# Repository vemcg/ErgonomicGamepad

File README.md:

# ErgonomicGamepad

Custom ergonomic gaming keypad PCB project (KiCad) with a 4x6 key matrix, hot-swap sockets, and USB-C.

## Overview

This repo contains the schematic, PCB, and production support files for an ATmega32U4-based ergonomic keypad.

## Hardware Summary

| Item | Value |
|---|---|
| MCU | ATmega32U4 (TQFP-44) |
| Key Matrix | 4 rows x 6 columns (24 keys) |
| Switch Interface | MX-compatible Kailh hot-swap sockets |
| USB | USB-C receptacle |
| Clock | 16 MHz crystal |
| Passive Size | 0603 resistors/capacitors |
| Protection/Diodes | 1N4148 matrix diodes, 1N5819WS Schottky |

## Core Project Files

- `ErgonomicGamepad.kicad_sch` - Schematic
- `ErgonomicGamepad.kicad_pcb` - PCB layout
- `ErgonomicGamepad.kicad_pro` - KiCad project
- `jlcpcb/production_files/jlc_sourcing_bom_template.csv` - Main sourcing/BOM table
- `jlcpcb/production_files/verify_stock_before_ordering.csv` - Pre-order stock/sourcing risk checklist (MCU lead time, hand-sourced sockets/connectors/switches)
- `jlcpcb/gerber/` - Manufacturing output folder

## Pinout Baseline

### Matrix

| Signal | Pins |
|---|---|
| ROW1-ROW4 | PF7, PF6, PF5, PF4 |
| COL1-COL6 | PD1, PD2, PD3, PD4, PD5, PD6 |

### Programming Header (ISP)

| Signal | Pin Mapping |
|---|---|
| SCK | PB1 |
| MOSI | PB2 |
| MISO | PB3 |
| RESET | J5 pin 5 -> U1 ~RESET |

## USB-C Implementation (Resolved)

J1 is an HRO `TYPE-C-31-M-12` receptacle - hybrid retention (SMT signal/power
pins plus through-hole shell tabs) for stronger cable-insertion durability
than an SMT-only part. This is a USB 2.0 device-only implementation (power +
D+/D-); no SuperSpeed/Alt-Mode pins are used.

- **Orientation**: fully reversible. Both D+ pads (A6 and B6) are tied
  together at the connector, and both D- pads (A7 and B7) are tied together,
  so the plug works in either orientation.
- **Signal path**: connector D+/D- -> U2 (`USBLC6-2SC6` ESD protection array)
  -> series resistors R1/R2 (20R) -> U1 D-/D+ pins, with TP3/TP4 tapping the
  MCU-side D-/D+ nets for debug access.
- **CC (device-mode/UFP)**: CC1 and CC2 each pull down to GND through a 5.1k
  resistor (R4, R5) - the standard passive UFP presentation, no CC logic IC.
- **Shield/GND**: J1's shield pin (`SH`) ties directly to GND (no RC/ferrite
  isolation).
- **Power path**: VBUS feeds +5V through D1 (`1N5819WS` Schottky) gated by
  JP1 (power-path select jumper - see Jumper Shunts below); J7 (external
  2-pin power connector) feeds +5V directly. The Schottky prevents VBUS from
  being back-fed if J7 external power is connected while a USB cable is also
  plugged in.

## Debug / Test Points

- **TP1-TP7**: internal signal debug points (power-select node, GND
  reference, USB D+/D-, crystal XTAL1/XTAL2, USB regulator cap node) using
  the small `TestPoint_Pad_D1.5mm` footprint - sized for a fine meter probe
  or hook, not a full-size clip.
- **TP8 (+5V) / TP9 (GND)**: dedicated power-rail clip points, intended to
  be placed at the board edge for easy alligator-clip access during bring-up
  and testing. These use the larger `TestPoint_THTPad_D3.0mm_Drill1.5mm`
  footprint (a real drilled through-hole pad, not just a flat SMD pad) so an
  actual clip has something to bite onto. Kept separate from TP2 (which
  stays with the internal signal-debug cluster near the MCU) since GND is a
  single net and a second access point elsewhere costs nothing electrically.

## Footprint Baseline (Current)

- SW1-SW24: `Switch_Keyboard_Hotswap_Kailh:SW_Hotswap_Kailh_MX_Plated_1.00u`
- J1: `Connector_USB:USB_C_Receptacle_HRO_TYPE-C-31-M-12`
- R1-R7: `Resistor_SMD:R_0603_1608Metric`
- C1-C5: `Capacitor_SMD:C_0603_1608Metric`
- D25-D26: `LED_SMD:LED_0603_1608Metric`
- TP1-TP7: `TestPoint:TestPoint_Pad_D1.5mm`
- TP8/TP9: `TestPoint:TestPoint_THTPad_D3.0mm_Drill1.5mm` (edge-mounted power/ground clip points - see Debug / Test Points above)
- J2/J3/J4/J6: `Connector_JST:JST_XH_B5B-XH-A_1x05_P2.50mm_Vertical` (DNP - see Satellite Board Cables below)
- J7: `PinHeader_1x02_P2.54mm_Vertical`
- J5: `PinHeader_2x03_P2.54mm_Vertical`
- JP1/JP2: `Connector_PinHeader_2.54mm:PinHeader_1x02_P2.54mm_Vertical`
- Y1: `Crystal:Crystal_SMD_3215-2Pin_3.2x1.5mm`
- SWR1: `Button_Switch_SMD:SW_SPST_B3U-3000P`

## Jumper Shunts Needed (Not Part of PCBA)

JP1 (power-path select) and JP2 (forces hardware bootloader via U1 pin 33 /
HWB when bridged) are populated as bare 2-pin headers during JLCPCB assembly,
but the assembly process does not install a shunt on them - a jumper shunt is
a friction-fit plastic/metal cap, not a soldered part, so it has to be
installed by hand after the boards arrive.

Buy separately (not on the PCBA BOM):
- **2.54mm 2-pin jumper shunt cap** - e.g. BOOMELE, LCSC `C5305` (~$0.01/unit,
  50-piece minimum order on LCSC). Any standard 2.54mm/0.1" shunt works; this
  is a common commodity part also sold on Amazon/DigiKey/etc.
- Need at least 2 (one per jumper), but buy a small handful (the LCSC MOQ is
  50 anyway) since they're easy to lose.

## Switches & Keycaps Needed (Not Part of PCBA)

SW01-SW24 are Kailh MX hotswap sockets, soldered directly to the board (see
Footprint Baseline above), but the actual keyswitches and keycaps are
separate hand-sourced items that get plugged in after assembly - the whole
point of a hotswap board is that these aren't soldered.

- **Hotswap sockets** (on-board, hand-soldered): Kailh `CPG151101S11-16`,
  LCSC `C5156480` - https://www.lcsc.com/datasheet/C5156480.pdf. Currently
  shows near-zero LCSC stock (consignment-style listing), so plan to
  hand-source and hand-solder these rather than rely on JLCPCB
  auto-placement - see Progress notes below. Need 24 plus a few spares.
  Each socket takes 2 solder joints (through-hole); the extra alignment
  pins in the footprint hold it steady while soldering. For practical
  hobbyist purchasing, the real path is AliExpress - there are multiple
  listings selling genuine Kailh hotswap sockets in small hobbyist-friendly
  quantities (30/90/110-packs), which is how most individual keyboard
  builders actually buy these - or a specialty keyboard-parts retailer
  like splitkb.com, which stocks Kailh hotswap sockets specifically for
  this use case.
- **Keyswitches** (plug into the sockets, not soldered): Cherry MX Brown
  (tactile), official part `MX1A-G1NW`. Also frequently out of stock on
  LCSC - source from a specialty mechanical-keyboard parts retailer instead
  (e.g. KBDfans, NovelKeys, Mechanicalkeyboards.com, or similar). Since the
  socket is switch-agnostic (any standard MX-footprint switch fits), a
  well-regarded MX-compatible clone switch would also work if genuine
  Cherry isn't available. Need 24 plus a few spares.
- **Keycaps**: MX-compatible (cross-stem) keycaps, not yet specced -
  profile (OEM/Cherry/DSA/etc.), material, and colorway are a personal
  choice. Note this layout is a non-standard ergonomic 4x6 matrix, not a
  regular keyboard row layout, so a generic pre-made keycap set is unlikely
  to have correctly-sculpted keycaps for every position - uniform-profile
  (same shape regardless of position) or blank keycaps are the simplest
  option unless a custom set is planned.

## Satellite Board Cables Needed (Not Part of PCBA)

J2/J3/J4/J6 connect the two satellite switch boards to the main board (ROW1-4
+ COL1 per connector - no power needed, see Pinout Baseline). They're marked
DNP on the JLCPCB assembly BOM since through-hole headers get hand-soldered
after the boards arrive, same reasoning as the hotswap sockets above.

- **Male headers** (on-board, hand-soldered): JST-XH 5-pin, `B5B-XH-A`
  (matches the footprint above). Genuine JST stock from **Digi-Key** or
  **Mouser** (search `B5B-XH-A` directly), or cheaper from **LCSC/JLCPCB**
  (search "XH 5P" or the part number `B5B-XH-A(LF)(SN)`) - the latter is also
  orderable through JLCPCB assembly if DNP is ever lifted. Generic
  multi-packs from Amazon/AliExpress work fine too for prototyping. Need 4
  (one per connector) plus spares.
- **Female-to-female cables**: JST-XH 5-pin, both ends female, connecting
  each main-board header to its matching satellite-board header. Target
  length ~3-4in. Best sourced from **AliExpress** (search "JST XH 2.54 5 pin
  cable" - widely available in 10/15/20/30cm, some sellers offer custom
  lengths) or **Amazon** (search "JST XH 5 pin cable" - mostly RC/battery
  sellers, lengths cluster around 15-30cm with some 10cm/~4in options). If
  the exact length/pinout combo isn't available premade, a JST-XH crimp tool
  (~$15-20) plus loose housings/terminals (pennies each, same vendors) makes
  it easy to build the 2 needed cables to spec. Individual wires are
  flexible (stranded, not ribbon) so routing/twisting around the enclosure
  isn't a concern.

## Progress (Brief)

Done:
- Schematic is component-complete.
- Footprints assigned for all currently tracked parts.
- Schematic and PCB baseline are synced.
- ISP signal mapping corrected and documented.
- JLC sourcing workflow files are in place.
- USB-C orientation, CC, ESD, shield, and power-path decisions locked and documented.

Not done yet:
- Component placement refinement.
- PCB routing completion.
- Panelization/mechanical finalization.
- Final DRC-clean release candidate.
- Gerber/BOM/CPL release package for fabrication.
- Firmware development.

## Process Checklist

For the full detailed build, verification, and manufacturing checklist, use [PROCESS.md](PROCESS.md).

---

Last Updated: July 2026
Project Status: Pre-Layout Baseline

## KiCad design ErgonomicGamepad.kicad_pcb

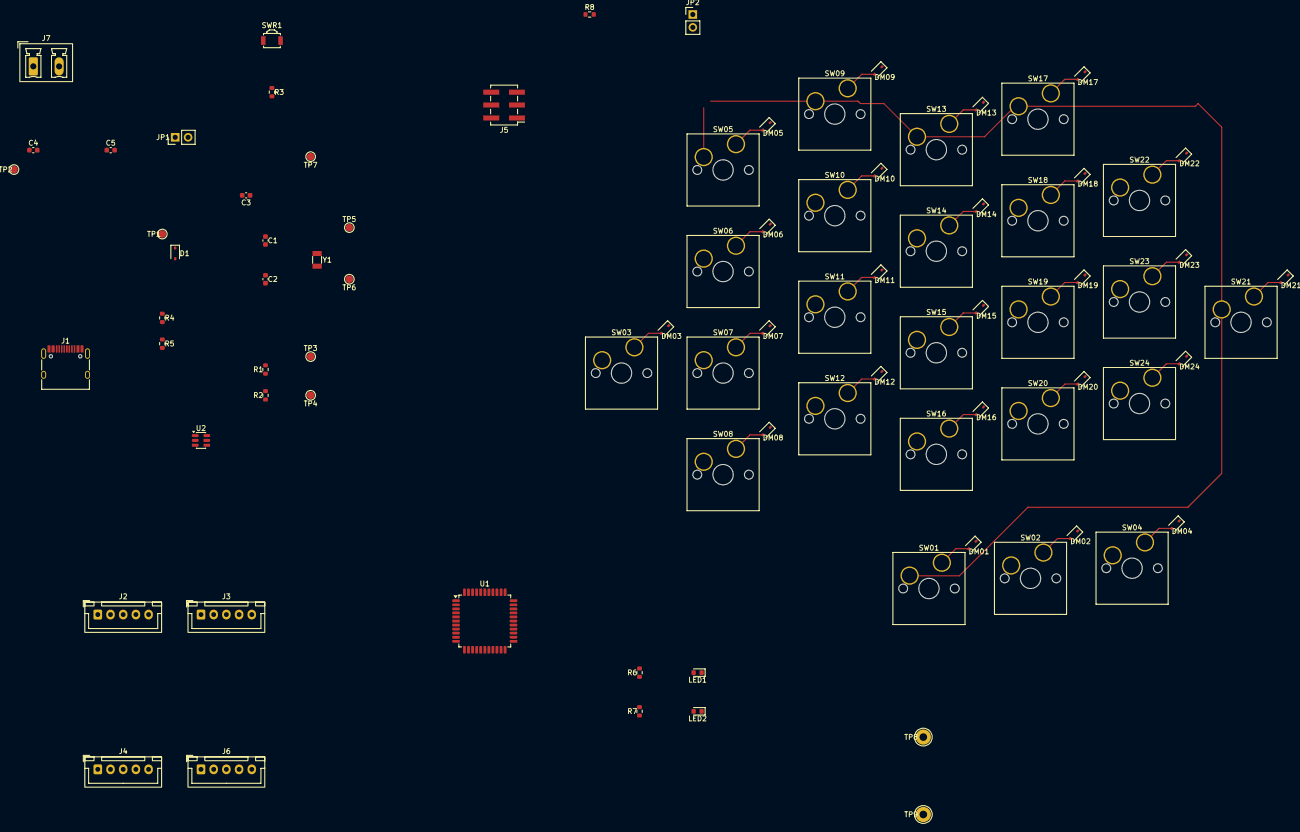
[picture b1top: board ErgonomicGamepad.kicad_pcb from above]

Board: 2 copper layers, 86 parts (0 on the bottom side), 57 nets.

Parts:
C1, C2: 22pF; C_0603_1608Metric
C3: 1uF; C_0603_1608Metric
C4: 4.7uF; C_0603_1608Metric
C5: 100nF; C_0603_1608Metric
D1: 1N5819WS; D_SOD-323
DM01, DM02, DM03, DM04, DM05, DM06, DM07, DM08, DM09, DM10, DM11, DM12, DM13, DM14, DM15, DM16, DM17, DM18, DM19, DM20, DM21, DM22, DM23, DM24: 1N4148WS; D_SOD-323
J1: USB_C_Receptacle_USB2.0_16P; USB_C_Receptacle_HRO_TYPE-C-31-M-12
J2, J3, J4, J6: Conn_01x05; JST_XH_B5B-XH-A_1x05_P2.50mm_Vertical
J5: AVR-ISP-6; PinHeader_2x03_P2.54mm_Vertical_SMD
J7: 1824417; PhoenixContact_MCV_1,5_2-G-5.08_1x02_P5.08mm_Vertical
JP1, JP2: Jumper_2_Open; PinHeader_1x02_P2.54mm_Vertical
LED1: LED Pwr; LED_0603_1608Metric
LED2: LED Dbg; LED_0603_1608Metric
R1, R2: 20R; R_0603_1608Metric
R3: 10K; R_0603_1608Metric
R4, R5: 5.1k; R_0603_1608Metric
R6: 1k; R_0603_1608Metric
R7: 330; R_0603_1608Metric
R8: 10k; R_0603_1608Metric
SW01, SW02, SW03, SW04, SW05, SW06, SW07, SW08, SW09, SW10, SW11, SW12, SW13, SW14, SW15, SW16, SW17, SW18, SW19, SW20, SW21, SW22, SW23, SW24: SW_DIP_x01; SW_Hotswap_Kailh_MX_Plated_1.00u
SWR1: B3U-3000P; SW_SPST_B3U-3000P
TP1, TP2, TP3, TP4, TP5, TP6, TP7: TestPoint; TestPoint_Pad_D1.5mm
TP8, TP9: TestPoint; TestPoint_THTPad_D3.0mm_Drill1.5mm
U1: ATmega32U4-A; TQFP-44_10x10mm_P0.8mm
U2: USBLC6-2SC6; SOT-23-6
Y1: Crystal; Crystal_SMD_3215-2Pin_3.2x1.5mm

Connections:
+5V: C4.1, C5.1, J5.2 (VCC), J7.1, JP1.2 (B), R3.2, R6.1, R8.1, TP8.1 (1_1), U1.2 (UVCC), U1.7 (VBUS), U1.14 (VCC), U1.24 (AVCC), U1.34 (VCC), U1.42 (AREF), U1.44 (AVCC)
/COL1: DM01.1 (K), DM02.1 (K), DM03.1 (K), DM04.1 (K), J2.5, J3.5, J4.5, J6.5, U1.22 (PD5)
/COL2: DM05.1 (K), DM06.1 (K), DM07.1 (K), DM08.1 (K), U1.25 (PD4)
/COL3: DM09.1 (K), DM10.1 (K), DM11.1 (K), DM12.1 (K), U1.21 (PD3)
/COL4: DM13.1 (K), DM14.1 (K), DM15.1 (K), DM16.1 (K), U1.20 (PD2)
/COL5: DM17.1 (K), DM18.1 (K), DM19.1 (K), DM20.1 (K), U1.19 (PD1)
/COL6: DM21.1 (K), DM22.1 (K), DM23.1 (K), DM24.1 (K), U1.18 (PD0)
/D+: R2.2, TP4.1 (1_1), U1.4 (D+)
/D-: R1.2, TP3.1 (1_1), U1.3 (D-)
/HWB: JP2.1 (A), R8.2, U1.33 (~HWB/PE2)
/MISO: J5.1 (MISO), U1.11 (PB3)
/MOSI: J5.4 (MOSI), U1.10 (PB2)
/RESET: J5.5 (~RST), R3.1, SWR1.2, U1.13 (~RESET)
/ROW1: J2.1, J3.1, J4.1, J6.1, SW01.1, SW05.1, SW09.1, SW13.1, SW17.1, SW21.1, U1.41 (PF0)
/ROW2: J2.2, J3.2, J4.2, J6.2, SW02.1, SW06.1, SW10.1, SW14.1, SW18.1, SW22.1, U1.40 (PF1)
/ROW3: J2.3, J3.3, J4.3, J6.3, SW03.1, SW07.1, SW11.1, SW15.1, SW19.1, SW23.1, U1.39 (PF4)
/ROW4: J2.4, J3.4, J4.4, J6.4, SW04.1, SW08.1, SW12.1, SW16.1, SW20.1, SW24.1, U1.38 (PF5)
/SCK: J5.3 (SCK), U1.9 (PB1)
/UCAP: C3.2, TP7.1 (1_1), U1.6 (UCAP)
/VBUS RAW: D1.2 (A), J1.A4 (VBUS), J1.A9 (VBUS), J1.B4 (VBUS), J1.B9 (VBUS), U2.5 (VBUS)
/XTAL1: C1.1, TP5.1 (1_1), U1.17 (XTAL1), Y1.1
/XTAL2: C2.1, TP6.1 (1_1), U1.16 (XTAL2), Y1.2
GND: C1.2, C2.2, C3.1, C4.2, C5.2, J1.A1 (GND), J1.A12 (GND), J1.B1 (GND), J1.B12 (GND), J1.SH (SHIELD), J5.6 (GND), J7.2, JP2.2 (B), LED1.1 (K), LED2.1 (K), R4.1, R5.1, SWR1.1, TP2.1 (1_1), TP9.1 (1_1), U1.5 (UGND), U1.15 (GND), U1.23 (GND), U1.35 (GND), U1.43 (GND), U2.2 (GND)
unnamed: D1.1 (K), JP1.1 (A), TP1.1 (1_1)
unnamed: DM01.2 (A), SW01.2
unnamed: DM02.2 (A), SW02.2
unnamed: DM03.2 (A), SW03.2
unnamed: DM04.2 (A), SW04.2
unnamed: DM05.2 (A), SW05.2
unnamed: DM06.2 (A), SW06.2
unnamed: DM07.2 (A), SW07.2
unnamed: DM08.2 (A), SW08.2
unnamed: DM09.2 (A), SW09.2
unnamed: DM10.2 (A), SW10.2
unnamed: DM11.2 (A), SW11.2
unnamed: DM12.2 (A), SW12.2
unnamed: DM13.2 (A), SW13.2
unnamed: DM14.2 (A), SW14.2
unnamed: DM15.2 (A), SW15.2
unnamed: DM16.2 (A), SW16.2
unnamed: DM17.2 (A), SW17.2
unnamed: DM18.2 (A), SW18.2
unnamed: DM19.2 (A), SW19.2
unnamed: DM20.2 (A), SW20.2
unnamed: DM21.2 (A), SW21.2
unnamed: DM22.2 (A), SW22.2
unnamed: DM23.2 (A), SW23.2
unnamed: DM24.2 (A), SW24.2
unnamed: J1.A5 (CC1), R4.2
unnamed: J1.B5 (CC2), R5.2
unnamed: J1.A6 (D+), J1.B6 (D+), U2.3 (I/O2)
unnamed: J1.A7 (D-), J1.B7 (D-), U2.1 (I/O1)
unnamed: LED1.2 (A), R6.2
unnamed: LED2.2 (A), R7.2
unnamed: R1.1, U2.6 (I/O1)
unnamed: R2.1, U2.4 (I/O2)
unnamed: R7.1, U1.1 (PE6)

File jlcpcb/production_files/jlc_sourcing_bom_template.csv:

"Quantity","Value","Footprint","References","LCSC","MPN","Manufacturer","Assembly","Notes"
"1","ATmega32U4-A","Package_QFP:TQFP-44_10x10mm_P0.8mm","U1","C44854","ATMEGA32U4-AU","Microchip","JLC_SMT","Critical long-lead item; confirm live stock before finalizing order"
"1","USBLC6-2SC6","Package_TO_SOT_SMD:SOT-23-6","U2","C7519","USBLC6-2SC6","STMicroelectronics","JLC_SMT",""
"1","Crystal","Crystal:Crystal_SMD_3215-2Pin_3.2x1.5mm","Y1","C13738","X322516MLB4SI","YXC Crystal Oscillators","JLC_SMT",""
"1","USB_C_Receptacle_USB2.0_16P","Connector_USB:USB_C_Receptacle_HRO_TYPE-C-31-M-12","J1","C165948","TYPE-C-31-M-12","Korean Hroparts Elec","JLC_SMT",""
"1","AVR-ISP-6","Connector_PinHeader_2.54mm:PinHeader_2x03_P2.54mm_Vertical_SMD","J5","C32713283","HX PZ2.54-2x3P TP","hanxia","JLC_SMT",""
"1","1824417","Connector_Phoenix_MC_HighVoltage:PhoenixContact_MCV_1,5_2-G-5.08_1x02_P5.08mm_Vertical","J7","C5873683","1824417","Phoenix Contact","JLC_SMT",""
"2","Jumper_2_Open","Connector_PinHeader_2.54mm:PinHeader_1x02_P2.54mm_Vertical","JP1,JP2","C124375","B-2100S02P-A110","Ckmtw","JLC_SMT","Bare header only; JLCPCB does not install a shunt cap - buy separately and hand-install (see README Jumper Shunts section)"
"1","1N5819WS","Diode_SMD:D_SOD-323","D1","C191023","1N5819WS","Guangdong Hottech","JLC_SMT",""
"24","1N4148WS","Diode_SMD:D_SOD-323","DM01,DM02,DM03,DM04,DM05,DM06,DM07,DM08,DM09,DM10,DM11,DM12,DM13,DM14,DM15,DM16,DM17,DM18,DM19,DM20,DM21,DM22,DM23,DM24","C917117","1N4148WS","JSMSEMI","JLC_SMT",""
"1","LED Pwr","LED_SMD:LED_0603_1608Metric","LED1","C19273151","YLED0603G","YONGYUTAI","JLC_SMT",""
"1","LED Dbg","LED_SMD:LED_0603_1608Metric","LED2","C2286","KT-0603R","Hubei KENTO Elec","JLC_SMT",""
"2","22pF","Capacitor_SMD:C_0603_1608Metric","C1,C2","C519390","CC0603JRNPO8BN220","YAGEO","JLC_SMT",""
"1","1uF","Capacitor_SMD:C_0603_1608Metric","C3","C106215","CC0603KRX5R7BB105","YAGEO","JLC_SMT",""
"1","4.7uF","Capacitor_SMD:C_0603_1608Metric","C4","C109456","CC0603KRX5R6BB475","YAGEO","JLC_SMT",""
"1","100nF","Capacitor_SMD:C_0603_1608Metric","C5","C14663","CC0603KRX7R9BB104","YAGEO","JLC_SMT",""
"2","20R","Resistor_SMD:R_0603_1608Metric","R1,R2","C125758","RC0603FR-0720RL","YAGEO","JLC_SMT",""
"1","10K","Resistor_SMD:R_0603_1608Metric","R3","C98220","RC0603FR-0710KL","YAGEO","JLC_SMT",""
"2","5.1k","Resistor_SMD:R_0603_1608Metric","R4,R5","C105580","RC0603FR-075K1L","YAGEO","JLC_SMT",""
"1","1k","Resistor_SMD:R_0603_1608Metric","R6","C22548","RC0603FR-071KL","YAGEO","JLC_SMT",""
"1","330","Resistor_SMD:R_0603_1608Metric","R7","C105881","RC0603FR-07330RL","YAGEO","JLC_SMT",""
"1","10k","Resistor_SMD:R_0603_1608Metric","R8","C98220","RC0603FR-0710KL","YAGEO","JLC_SMT",""
"1","B3U-3000P","Button_Switch_SMD:SW_SPST_B3U-3000P","SWR1","C963349","B3U-3000P","Omron","JLC_SMT",""
"24","SW_DIP_x01","Switch_Keyboard_Hotswap_Kailh:SW_Hotswap_Kailh_MX_Plated_1.00u","SW01,SW02,SW03,SW04,SW05,SW06,SW07,SW08,SW09,SW10,SW11,SW12,SW13,SW14,SW15,SW16,SW17,SW18,SW19,SW20,SW21,SW22,SW23,SW24","C5156480","CPG151101S11-16","Kailh","DNP_HAND_SOLDER","LCSC listing is near-zero/consignment stock - hand-source from AliExpress or splitkb.com and hand-solder after assembly (see README Switches & Keycaps Needed); need 24 plus spares"
"4","Conn_01x05","Connector_JST:JST_XH_B5B-XH-A_1x05_P2.50mm_Vertical","J2,J3,J4,J6","C157991","B5B-XH-A(LF)(SN)","JST","DNP_HAND_SOLDER","Hand-solder after boards arrive; order male headers from Digi-Key/Mouser/LCSC and matching female-to-female JST-XH cables separately (see README Satellite Board Cables Needed); need 4 plus spares"
"7","TestPoint","TestPoint:TestPoint_Pad_D1.5mm","TP1,TP2,TP3,TP4,TP5,TP6,TP7",,,,"BARE_PCB","No placed component; in_bom=no, excluded from assembly BOM by design"

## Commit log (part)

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2026-06-16 Add KiCad project scaffolding
    Initialize the project container for ErgonomicGamepad with the KiCad project file, PCB placeholder, project settings, and local ignore rules for history, backups, lock files, and caches.
    This keeps the repository baseline separate from the schematic content.
2026-06-16 Add ErgonomicGamepad schematic
    Add the live schematic for the ergonomic gamepad design, including the verified USB-C power path, ATmega32U4 controller, matrix diodes, connectors, and footprint assignments.
    This commit captures the circuit definition separately from the project scaffolding so future schematic edits are easy to review.
2026-06-16 Add project README
    Comprehensive documentation covering project overview, hardware specifications, status, getting started instructions, and design inspiration.
2026-06-25 Update symbols to KiCad 10 library versions
